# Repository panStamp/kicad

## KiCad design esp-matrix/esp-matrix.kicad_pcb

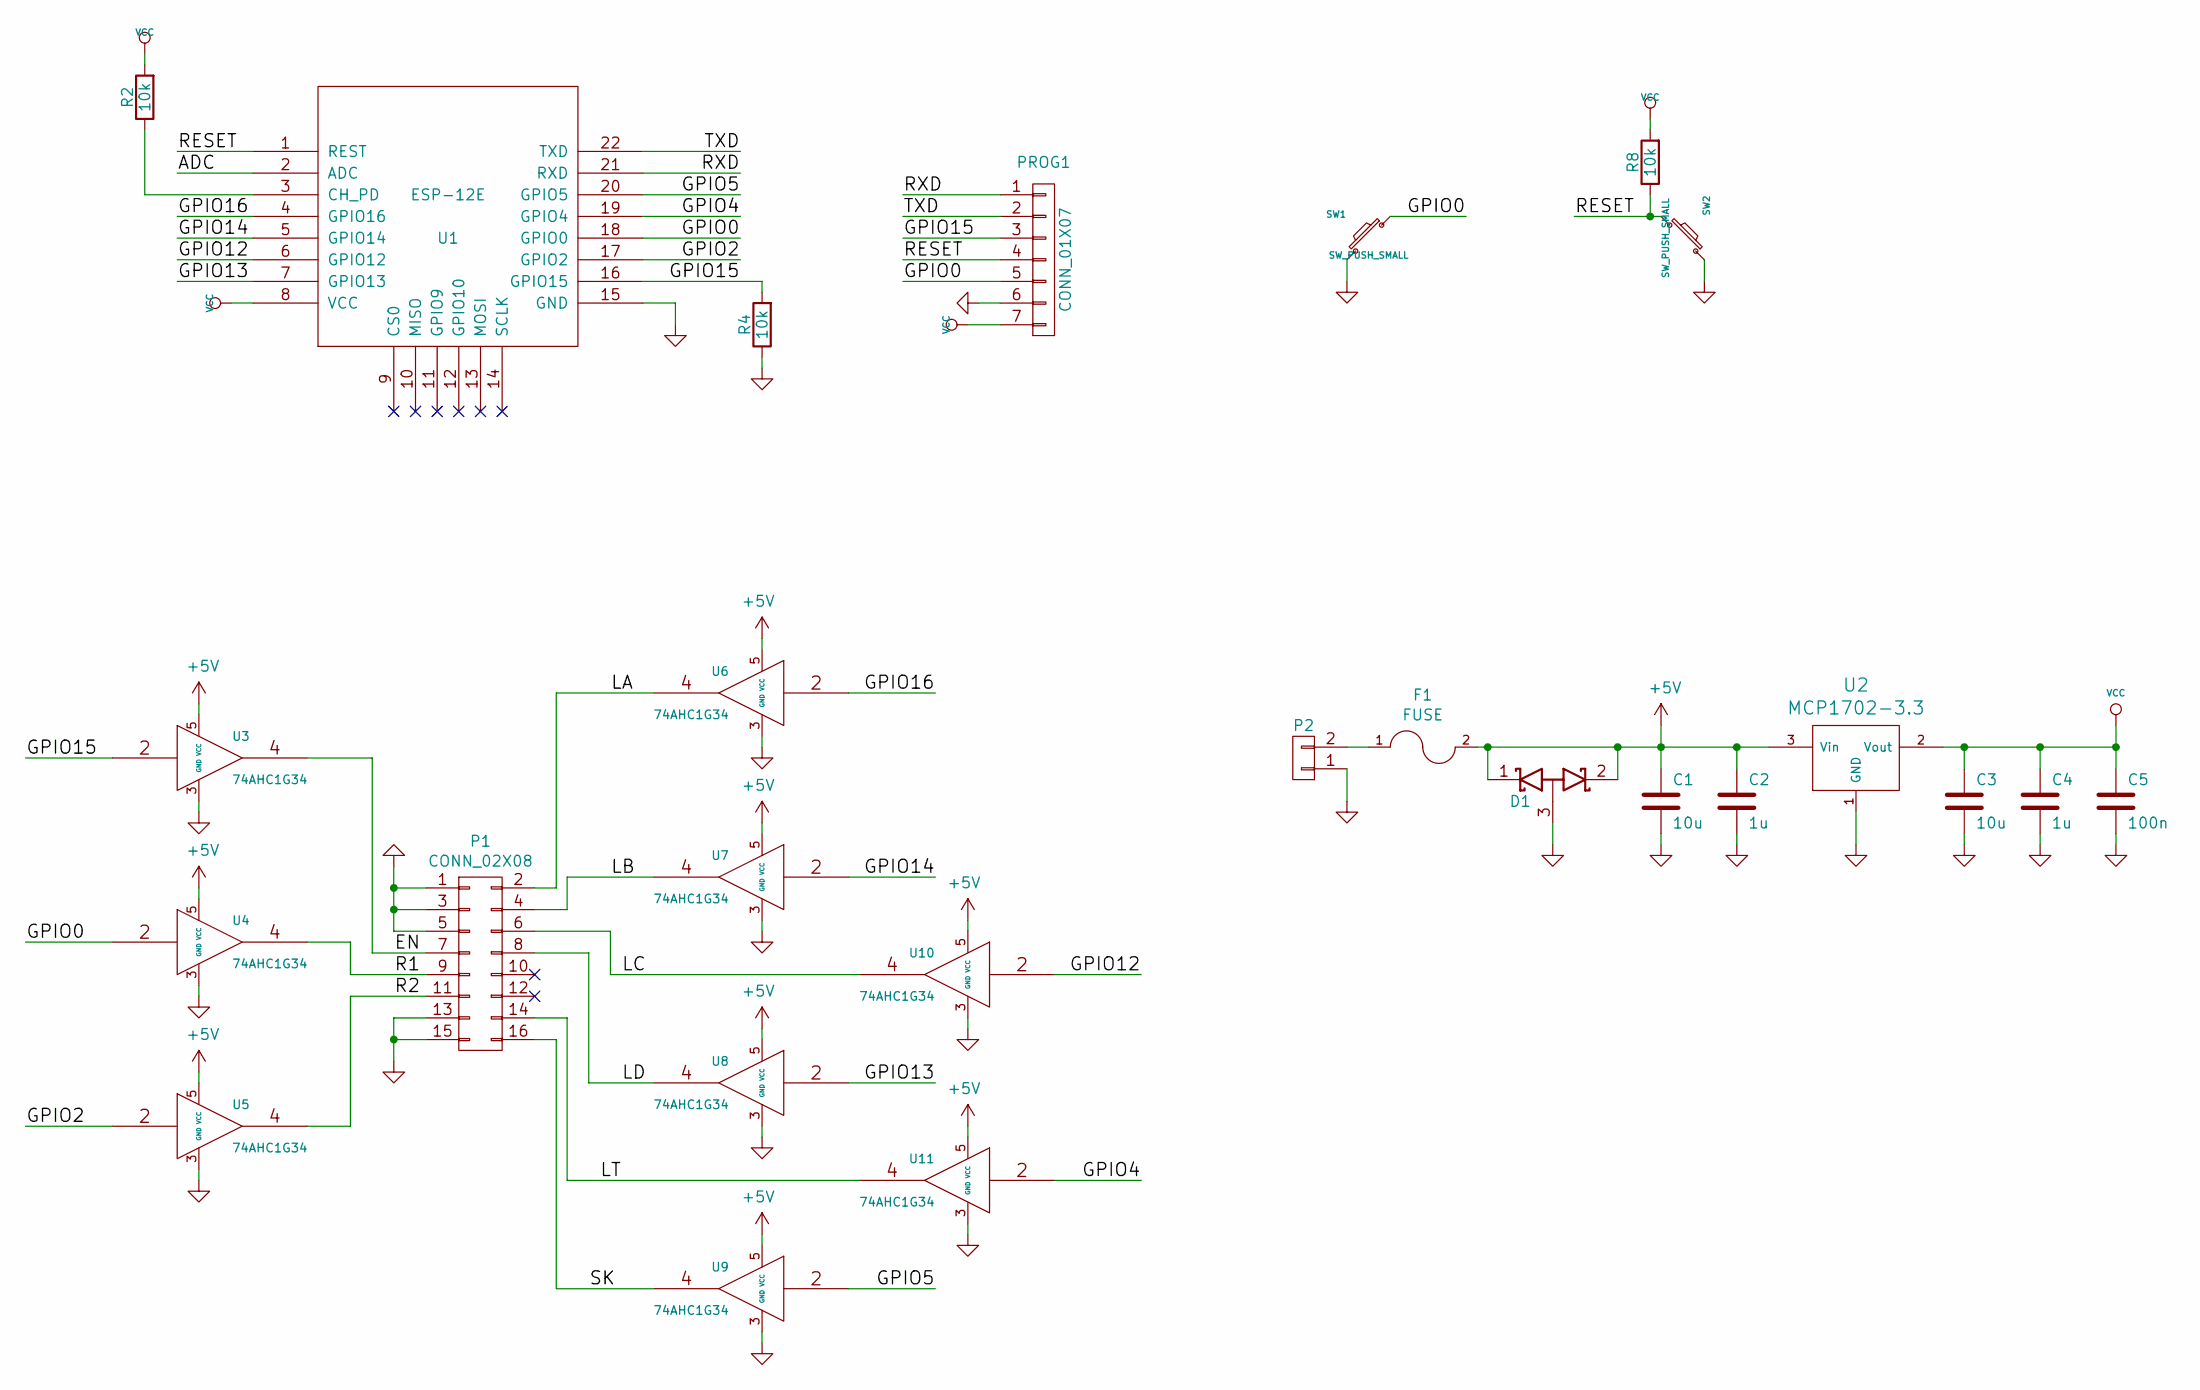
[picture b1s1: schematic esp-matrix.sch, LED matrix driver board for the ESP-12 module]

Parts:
C1, C3: 10u; SM0603S
C2, C4: 1u; SM0603S
C5: 100n; SM0603S
D1: D_Schottky_x2_ACom_KKA; SOT23
F1: FUSE; SM0805
P1: CONN_02X08; Pin_Header_Straight_2x08
P2: CONN_01X02; terminal_block_5mm_2P
PROG1: CONN_01X07; pinhead-1-1X07
R2, R4, R8: 10k; SM0603S
SW1, SW2: SW_PUSH_SMALL; switch-tact-noah
U1: ESP-12E
U2: MCP1702-3.3; SOT23
U3, U4, U5, U6, U7, U8, U9, U10, U11: 74AHC1G34; SOT23-5

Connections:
+5V: C1.1, C2.1, D1.1 (K), D1.2 (K), F1.2, U2.3 (Vin), U3.5 (VCC), U4.5 (VCC), U5.5 (VCC), U6.5 (VCC), U7.5 (VCC), U8.5 (VCC), U9.5 (VCC), U10.5 (VCC), U11.5 (VCC)
/ADC: U1.2 (ADC)
/EN: P1.7, U3.4
/GPIO0: PROG1.5, SW1.1, U1.18 (GPIO0), U4.2
/GPIO2: U1.17 (GPIO2), U5.2
/GPIO4: U1.19 (GPIO4), U11.2
/GPIO5: U1.20 (GPIO5), U9.2
/GPIO12: U1.6 (GPIO12), U10.2
/GPIO13: U1.7 (GPIO13), U8.2
/GPIO14: U1.5 (GPIO14), U7.2
/GPIO15: PROG1.3, R4.2, U1.16 (GPIO15), U3.2
/GPIO16: U1.4 (GPIO16), U6.2
/LA: P1.2, U6.4
/LB: P1.4, U7.4
/LC: P1.6, U10.4
/LD: P1.8, U8.4
/LT: P1.14, U11.4
/R1: P1.9, U4.4
/R2: P1.11, U5.4
/RESET: PROG1.4, R8.1, SW2.2, U1.1 (REST)
/RXD: PROG1.1, U1.21 (RXD)
/SK: P1.16, U9.4
/TXD: PROG1.2, U1.22 (TXD)
GND: C1.2, C2.2, C3.2, C4.2, C5.2, D1.3 (A), P1.1, P1.3, P1.5, P1.13, P1.15, P2.1, PROG1.6, R4.1, SW1.2, SW2.1, U1.15 (GND), U2.1 (GND), U3.3 (GND), U4.3 (GND), U5.3 (GND), U6.3 (GND), U7.3 (GND), U8.3 (GND), U9.3 (GND), U10.3 (GND), U11.3 (GND)
unnamed: F1.1, P2.2
unnamed: R2.1, U1.3 (CH_PD)
VCC: C3.1, C4.1, C5.1, PROG1.7, R2.2, R8.2, U1.8 (VCC), U2.2 (Vout)

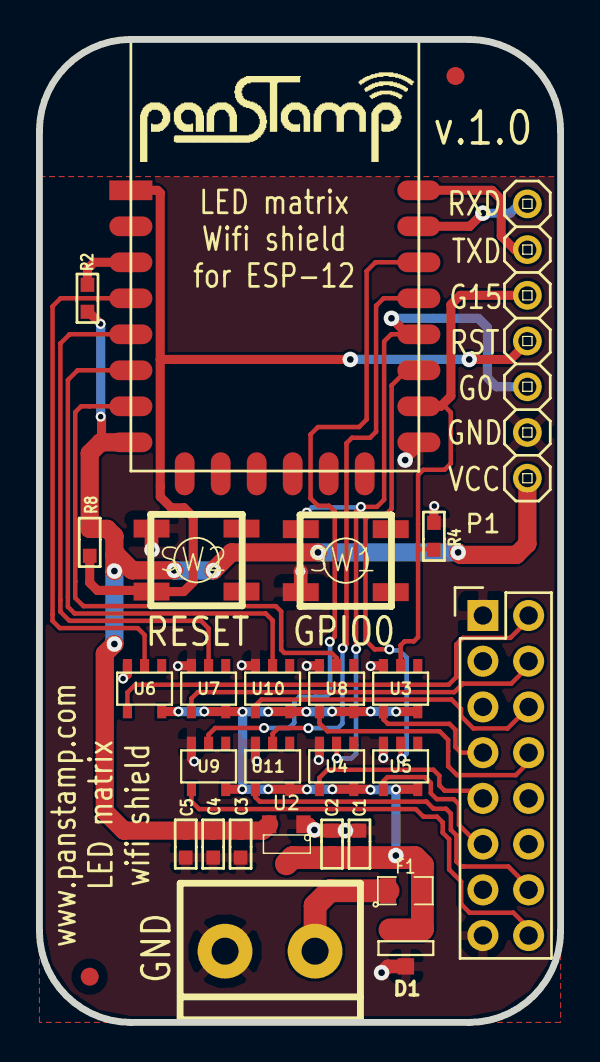
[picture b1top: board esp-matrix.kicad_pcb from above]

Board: 2 copper layers, 29.0 x 54.6 mm, 28 parts (0 on the bottom side), 26 nets.

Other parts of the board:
fiducial: VAL**; fiducial
fiducial#2: VAL**; fiducial

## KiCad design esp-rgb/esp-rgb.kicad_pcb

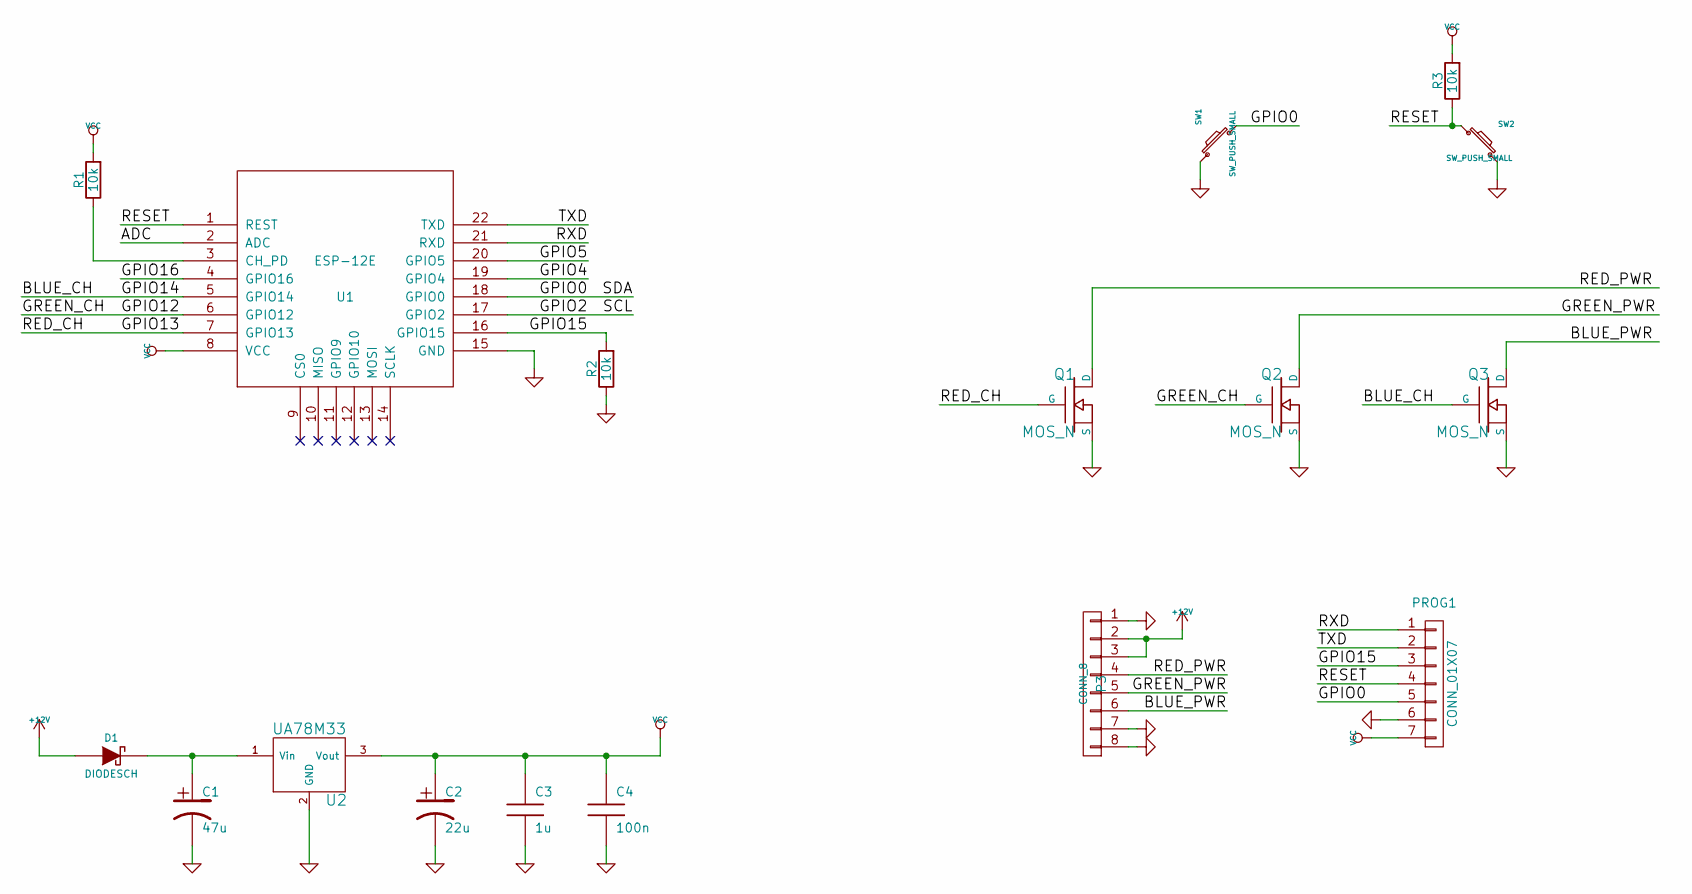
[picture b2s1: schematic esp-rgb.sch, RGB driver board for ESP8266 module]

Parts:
C1: 47u; SMDCPOL_6.3
C2: 22u; SMDCPOL_5
C3: 1u; SM0603S
C4: 100n; SM0603S
D1: DIODESCH; SMA
P3: CONN_8; Pin_Header_Straight_1x08
PROG1: CONN_01X07; Pin_Header_Straight_1x07
Q1, Q2, Q3: MOS_N; SOT23GDS
R1, R2, R3: 10k; SM0603S
SW1, SW2: SW_PUSH_SMALL; switch-tact-noah
U1: ESP-12E
U2: UA78M33; SOT223

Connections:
+12V: D1.1 (A), P3.2, P3.3
/ADC: U1.2 (ADC)
/BLUE_CH: Q3.G, U1.5 (GPIO14)
/BLUE_PWR: P3.6, Q3.D
/GPIO0: PROG1.5, SW1.2, U1.18 (GPIO0)
/GPIO2: U1.17 (GPIO2)
/GPIO4: U1.19 (GPIO4)
/GPIO5: U1.20 (GPIO5)
/GPIO12: Q2.G, U1.6 (GPIO12)
/GPIO13: Q1.G, U1.7 (GPIO13)
/GPIO15: PROG1.3, R2.2, U1.16 (GPIO15)
/GPIO16: U1.4 (GPIO16)
/GREEN_PWR: P3.5, Q2.D
/RED_PWR: P3.4, Q1.D
/RESET: PROG1.4, R3.1, SW2.1, U1.1 (REST)
/RXD: PROG1.1, U1.21 (RXD)
/TXD: PROG1.2, U1.22 (TXD)
GND: C1.2, C2.2, C3.2, C4.2, P3.1, P3.7, P3.8, PROG1.6, Q1.S, Q2.S, Q3.S, R2.1, SW1.1, SW2.2, U1.15 (GND), U2.2 (GND), U2.4
unnamed: C1.1, D1.2 (K), U2.1 (Vin)
unnamed: R1.1, U1.3 (CH_PD)
VCC: C2.1, C3.1, C4.1, PROG1.7, R1.2, R3.2, U1.8 (VCC), U2.3 (Vout)

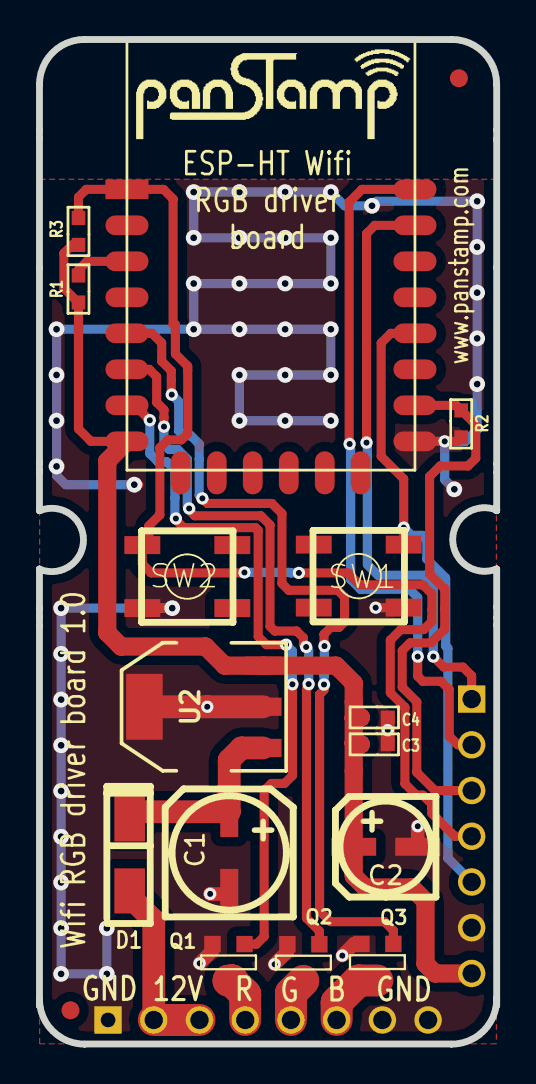
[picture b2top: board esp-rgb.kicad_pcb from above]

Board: 4 copper layers, 25.4 x 55.8 mm, 19 parts (0 on the bottom side), 16 nets.

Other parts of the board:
fiducial: VAL**; fiducial
fiducial#2: VAL**; fiducial

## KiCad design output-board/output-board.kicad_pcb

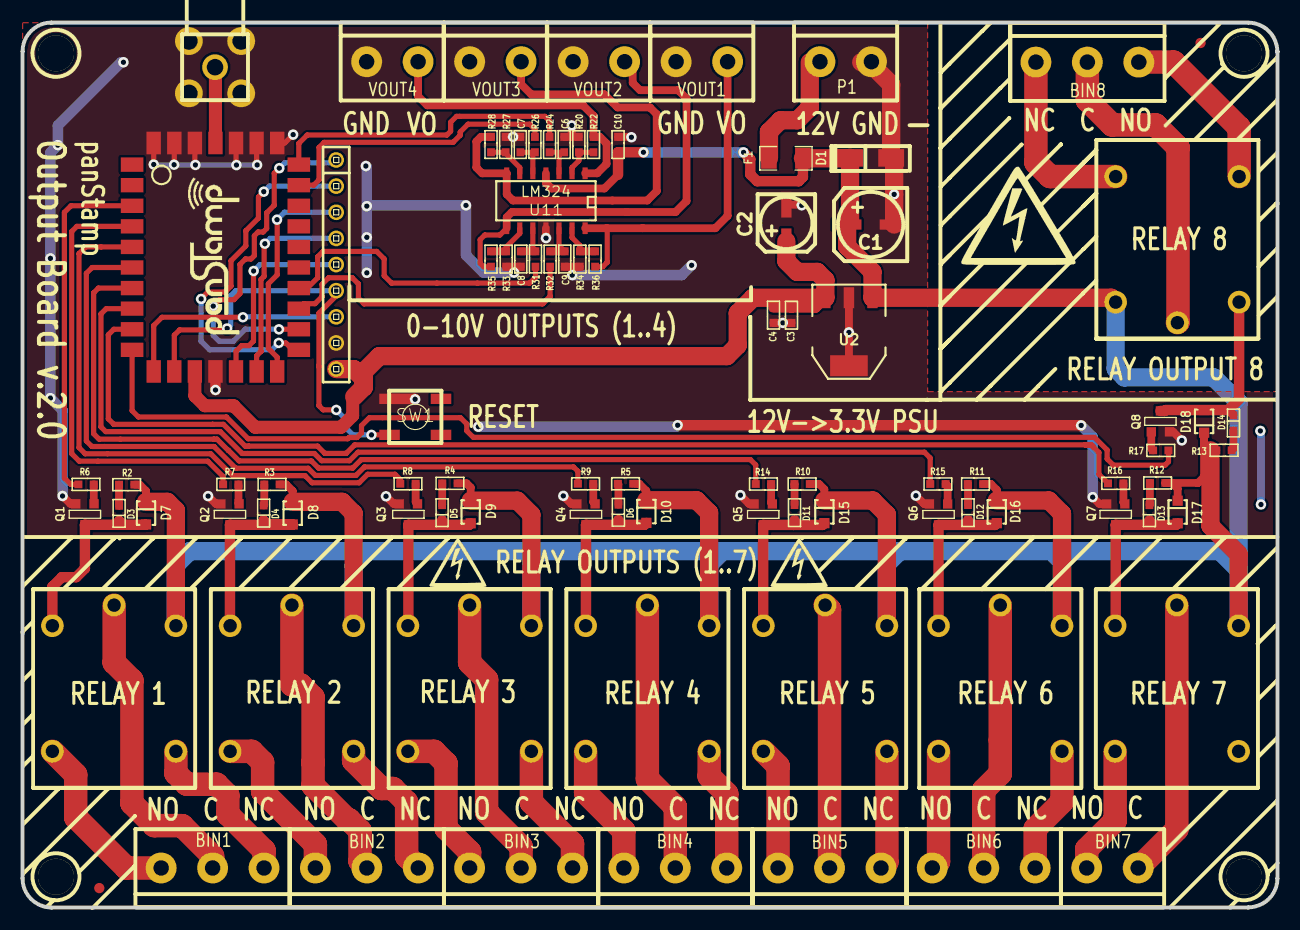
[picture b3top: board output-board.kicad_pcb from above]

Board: 2 copper layers, 121.9 x 86.0 mm, 96 parts (0 on the bottom side), 83 nets.

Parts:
1PIN, 1PIN#2, 1PIN#3, 1PIN#4: P***; 1pin
BIN1, BIN2, BIN3, BIN4, BIN5, BIN6, BIN8: CONN_3; terminal_block_5mm_3P
BIN7: CONN_2; terminal_block_5mm_2P
C1: 47u; SMDCPOL_6.3
C2: 22u; SMDCPOL_5
C3: 1u; SM0603S
C4, C10: 100n; SM0603S
C6, C7, C8, C9: 4.7u; SM0603S
D1: DIODESCH; SMA
D3, D4, D5, D6, D11, D12, D13, D14: LED; SM0603S_POL
D7, D8, D9, D10, D15, D16, D17, D18: DIODE; SOD323
F1: FUSE; SM1206
P1: CONN_2; terminal_block_5mm_2P
P2: CONN_01X09; pinhead-1X09
PS1: PANSTAMP_NRG2; PANSTAMP_2
Q1, Q2, Q3, Q4, Q5, Q6, Q7, Q8: NPN; SOT23EBC
R2, R3, R4, R5, R10, R11, R12, R13: 1k5; SM0603S
R6, R7, R8, R9, R14, R15, R16, R17: 2k2; SM0603S
R20, R27, R33, R34: 10k; SM0603S
R22, R28, R35, R36: 21k; SM0603S
R24, R26, R31, R32: 10K; SM0603S
SW1: SW_PUSH_SMALL; switch-tact-noah
U1: ANTENNA; SMA_RightAngle_Tyco
U2: UA78M33; SOT223
U3, U4, U5, U6, U7, U8, U9, U10: SONGLE_RELAY_10A
U11: LM324; SO14E
VOUT1, VOUT2, VOUT3, VOUT4: CONN_2; terminal_block_5mm_2P
fiducial: VAL**; fiducial
fiducial#2: VAL**; fiducial

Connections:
+3.3V: C2.1, C3.1, C4.1, P2.9, PS1.13, U2.3
+12V: C1.1, C10.1, D1.2, D7.2, D8.2, D9.2, D10.2, D15.2, D16.2, D17.2, D18.2, F1.2, R2.2, R3.1, R4.1, R5.1, R10.1, R11.1, R12.1, R13.1, U2.1, U3.1, U4.1, U5.1, U6.1, U7.1, U8.1, U9.1, U10.1, U11.4
/D7: P2.5, PS1.15
/RESET: P2.6, PS1.12, SW1.2
/RXD: P2.3, PS1.17
/SCL: P2.2, PS1.18
/SDA: P2.1, PS1.19
/TEST: P2.7, PS1.11
/TXD: P2.4, PS1.16
BINOUT0: PS1.3, R6.1
BINOUT1: PS1.4, R7.1
BINOUT2: PS1.5, R8.1
BINOUT3: PS1.6, R9.1
BINOUT4: PS1.7, R14.1
BINOUT5: PS1.8, R15.1
BINOUT6: PS1.9, R16.1
BINOUT7: PS1.10, R17.1
GND: C1.2, C2.2, C3.2, C4.2, C6.2, C7.2, C8.2, C9.2, C10.2, D1.1, P1.1, P2.8, PS1.14, PS1.28, PS1.29, PS1.30, PS1.32, PS1.33, PS1.34, Q1.1, Q2.1, Q3.1, Q4.1, Q5.1, Q6.1, Q7.1, Q8.1, R20.1, R27.1, R33.1, R34.1, SW1.1, U1.2, U2.2, U2.4, U11.11, VOUT1.2, VOUT2.2, VOUT3.2, VOUT4.2
unnamed: BIN1.1, U3.4
unnamed: BIN1.2, U3.2
unnamed: BIN1.3, U3.5
unnamed: BIN2.1, U4.4
unnamed: BIN2.2, U4.2
unnamed: BIN2.3, U4.5
unnamed: BIN3.1, U5.4
unnamed: BIN3.2, U5.2
unnamed: BIN3.3, U5.5
unnamed: BIN4.1, U6.4
unnamed: BIN4.2, U6.2
unnamed: BIN4.3, U6.5
unnamed: BIN5.1, U7.4
unnamed: BIN5.2, U7.2
unnamed: BIN5.3, U7.5
unnamed: BIN6.1, U8.4
unnamed: BIN6.2, U8.2
unnamed: BIN6.3, U8.5
unnamed: BIN7.1, U9.4
unnamed: BIN7.2, U9.2
unnamed: BIN8.1, U10.4
unnamed: BIN8.2, U10.2
unnamed: BIN8.3, U10.5
unnamed: C6.1, R24.1, U11.3
unnamed: C7.1, R26.1, U11.5
unnamed: C8.1, R31.1, U11.10
unnamed: C9.1, R32.1, U11.12
unnamed: D3.1, R2.1
unnamed: D3.2, D7.1, Q1.3, U3.3
unnamed: D4.1, R3.2
unnamed: D4.2, D8.1, Q2.3, U4.3
unnamed: D5.1, R4.2
unnamed: D5.2, D9.1, Q3.3, U5.3
unnamed: D6.1, R5.2
unnamed: D6.2, D10.1, Q4.3, U6.3
unnamed: D11.1, R10.2
unnamed: D11.2, D15.1, Q5.3, U7.3
unnamed: D12.1, R11.2
unnamed: D12.2, D16.1, Q6.3, U8.3
unnamed: D13.1, R12.2
unnamed: D13.2, D17.1, Q7.3, U9.3
unnamed: D14.1, R13.2
unnamed: D14.2, D18.1, Q8.3, U10.3
unnamed: F1.1, P1.2
unnamed: PS1.31, U1.1
unnamed: Q1.2, R6.2
unnamed: Q2.2, R7.2
unnamed: Q3.2, R8.2
unnamed: Q4.2, R9.2
unnamed: Q5.2, R14.2
unnamed: Q6.2, R15.2
unnamed: Q7.2, R16.2
unnamed: Q8.2, R17.2
unnamed: R20.2, R22.1, U11.2
unnamed: R22.2, U11.1, VOUT4.1
unnamed: R27.2, R28.1, U11.6
unnamed: R28.2, U11.7, VOUT3.1
unnamed: R33.2, R35.1, U11.9
unnamed: R34.2, R36.1, U11.13
unnamed: R35.2, U11.8, VOUT2.1
unnamed: R36.2, U11.14, VOUT1.1
PWMOUT0: PS1.27, R24.2
PWMOUT1: PS1.26, R26.2
PWMOUT2: PS1.21, R31.2
PWMOUT3: PS1.20, R32.2

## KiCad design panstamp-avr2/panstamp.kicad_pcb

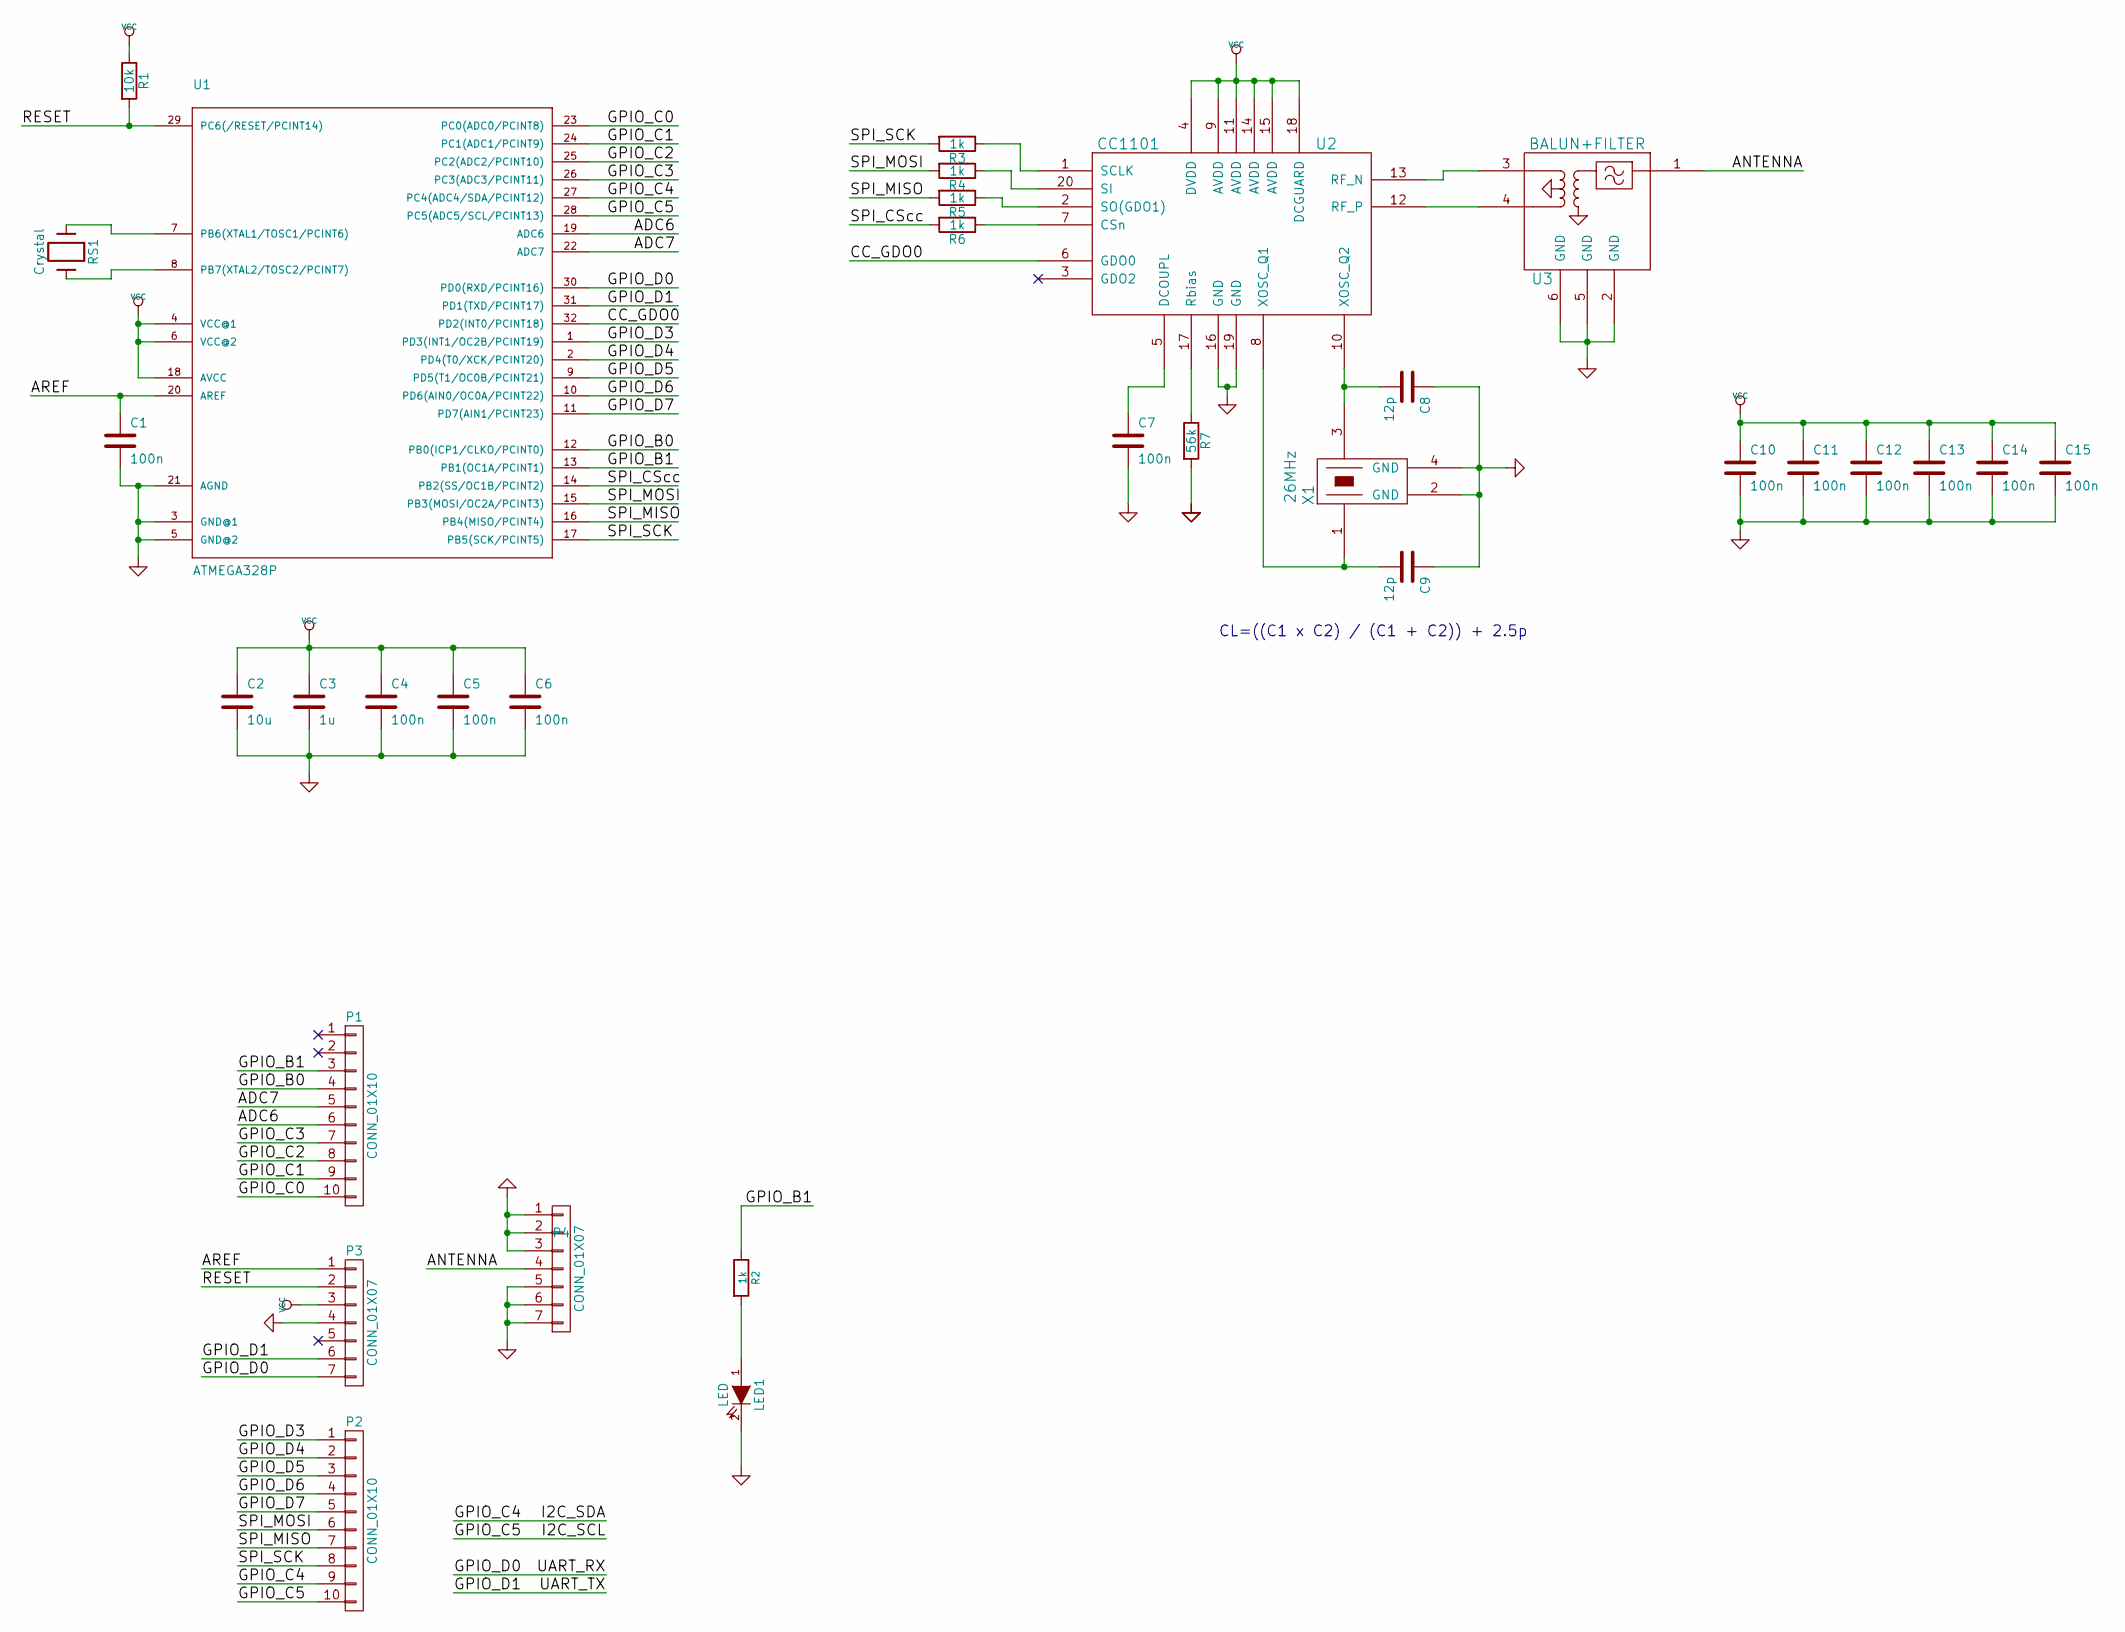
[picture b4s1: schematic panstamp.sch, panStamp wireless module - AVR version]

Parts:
C1, C4, C5, C6, C7, C10, C11, C12, C13, C14, C15: 100n; SM0603S
C2: 10u; SM0603S
C3: 1u; SM0603S
C8, C9: 12p; SM0603S
LED1: LED; SM0603S_POL
P1, P2: CONN_01X10; CASTELLATED_2MM_10
P3, P4: CONN_01X07; CASTELLATED_2MM_7
R1: 10k; SM0603S
R2, R3, R4, R5, R6: 1k; SM0603S
R7: 56k; SM0603S
RS1: Crystal
U1: ATMEGA328P; avr-MLF32
U2: CC1101; QLP20
U3: BALUN+FILTER; JTI_Balun
X1: 26MHz; FCX-162

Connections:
/ADC6: P1.6, U1.19 (ADC6)
/ADC7: P1.5, U1.22 (ADC7)
/ANTENNA: P4.4, U3.1
/AREF: C1.1, P3.1, U1.20 (AREF)
/CC_GDO0: U1.32 (PD2(INT0/PCINT18)), U2.6 (GDO0)
/GPIO_B0: P1.4, U1.12 (PB0(ICP1/CLKO/PCINT0))
/GPIO_B1: P1.3, R2.1, U1.13 (PB1(OC1A/PCINT1))
/GPIO_C0: P1.10, U1.23 (PC0(ADC0/PCINT8))
/GPIO_C1: P1.9, U1.24 (PC1(ADC1/PCINT9))
/GPIO_C2: P1.8, U1.25 (PC2(ADC2/PCINT10))
/GPIO_C3: P1.7, U1.26 (PC3(ADC3/PCINT11))
/GPIO_C4: P2.9, U1.27 (PC4(ADC4/SDA/PCINT12))
/GPIO_C5: P2.10, U1.28 (PC5(ADC5/SCL/PCINT13))
/GPIO_D0: P3.7, U1.30 (PD0(RXD/PCINT16))
/GPIO_D1: P3.6, U1.31 (PD1(TXD/PCINT17))
/GPIO_D3: P2.1, U1.1 (PD3(INT1/OC2B/PCINT19))
/GPIO_D4: P2.2, U1.2 (PD4(T0/XCK/PCINT20))
/GPIO_D5: P2.3, U1.9 (PD5(T1/OC0B/PCINT21))
/GPIO_D6: P2.4, U1.10 (PD6(AIN0/OC0A/PCINT22))
/GPIO_D7: P2.5, U1.11 (PD7(AIN1/PCINT23))
/RESET: P3.2, R1.2, U1.29 (PC6(/RESET/PCINT14))
/SPI_CScc: R6.2, U1.14 (PB2(SS/OC1B/PCINT2))
/SPI_MISO: P2.7, R5.2, U1.16 (PB4(MISO/PCINT4))
/SPI_MOSI: P2.6, R4.2, U1.15 (PB3(MOSI/OC2A/PCINT3))
/SPI_SCK: P2.8, R3.2, U1.17 (PB5(SCK/PCINT5))
GND: C1.2, C2.2, C3.2, C4.2, C5.2, C6.2, C7.2, C8.1, C9.1, C10.2, C11.2, C12.2, C13.2, C14.2, C15.2, LED1.2 (K), P3.4, P4.1, P4.2, P4.3, P4.5, P4.6, P4.7, R7.2, U1.3 (GND@1), U1.5 (GND@2), U1.21 (AGND), U2.16 (GND), U2.19 (GND), U3.2 (GND), U3.5 (GND), U3.6 (GND), X1.2 (GND), X1.4 (GND)
unnamed: C7.1, U2.5 (DCOUPL)
unnamed: C8.2, U2.10 (XOSC_Q2), X1.3
unnamed: C9.2, U2.8 (XOSC_Q1), X1.1
unnamed: LED1.1 (A), R2.2
unnamed: R3.1, U2.1 (SCLK)
unnamed: R4.1, U2.20 (SI)
unnamed: R5.1, U2.2 (SO(GDO1))
unnamed: R6.1, U2.7 (CSn)
unnamed: R7.1, U2.17 (Rbias)
unnamed: RS1.1, U1.7 (PB6(XTAL1/TOSC1/PCINT6))
unnamed: RS1.2, U1.8 (PB7(XTAL2/TOSC2/PCINT7))
unnamed: U2.12 (RF_P), U3.4
unnamed: U2.13 (RF_N), U3.3
VCC: C2.1, C3.1, C4.1, C5.1, C6.1, C10.1, C11.1, C12.1, C13.1, C14.1, C15.1, P3.3, R1.1, U1.4 (VCC@1), U1.6 (VCC@2), U1.18 (AVCC), U2.4 (DVDD), U2.9 (AVDD), U2.11 (AVDD), U2.14 (AVDD), U2.15 (AVDD), U2.18 (DCGUARD)

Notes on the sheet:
CL=((C1 x C2) / (C1 + C2)) + 2.5p

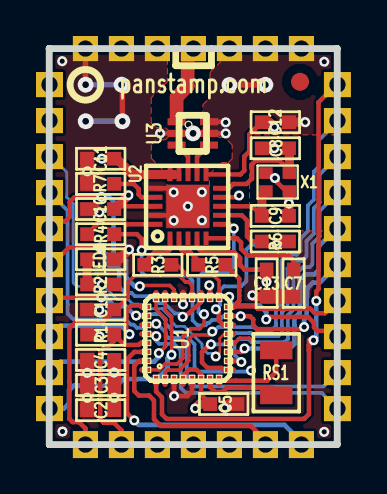
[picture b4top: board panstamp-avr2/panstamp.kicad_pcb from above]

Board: 4 copper layers, 16.0 x 22.0 mm, 30 parts (0 on the bottom side), 40 nets.

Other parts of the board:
fiducial: VAL**; fiducial

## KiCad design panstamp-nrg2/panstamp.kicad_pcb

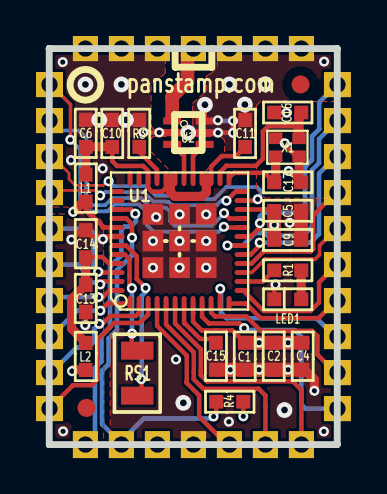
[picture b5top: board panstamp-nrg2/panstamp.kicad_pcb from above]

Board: 4 copper layers, 16.0 x 22.0 mm, 29 parts (0 on the bottom side), 40 nets.

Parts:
C1, C14: 10u; SM0603S
C2: 1u; SM0603S
C4, C5, C6, C11, C13: 100n; SM0603S
C9: 10n; SM0603S
C10: 2p; SM0603S
C15: 470nF; SM0603S
C16, C17: 12p; SM0603S
L1, L2: 600R/200mA; SM0603S
LED1: LED; SM0603S_POL
P1, P2: CONN_01X10; CASTELLATED_2MM_10
P3, P4: CONN_01X07; CASTELLATED_2MM_7
R1: 1k; SM0603S
R3: 56k(1%); SM0603S
R4: 47k; SM0603S
RS1: 32.768KHz; EPSON_F-135
U1: CC430F5137; VQFN48
U2: BALUN+FILTER; JTI_Balun
X1: 26MHz; FCX-162
fiducial: VAL**; fiducial
fiducial#2: VAL**; fiducial

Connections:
/#RST/SBWTDIO: P3.2, R4.2, U1.40
/ANTENNA: P4.4, U2.1
/I2C_SCL: P2.10, U1.9
/I2C_SDA: P2.9, U1.10
/P1.0: P2.6, U1.13
/P1.1: P2.7, U1.12
/P1.2: P2.8, U1.11
/P1.5: P3.7, U1.6
/P1.6: P3.6, U1.5
/P1.7: P3.5, U1.4
/P2.0/A0: P1.10, U1.3
/P2.1/A1: P1.9, U1.2
/P2.2/A2: P1.8, U1.1
/P2.3/A3: P1.7, U1.48
/P2.4/A4: P1.6, U1.47
/P2.5/A5: P1.5, U1.46
/P2.6: P1.4, U1.24
/P2.7: P1.3, U1.23
/P3.0: P1.2, U1.21
/P3.1: P1.1, U1.20
/P3.2: P2.1, U1.19
/P3.3: P2.2, U1.18
/P3.4: P2.3, U1.17
/P3.5: P2.4, U1.16
/P3.6: P2.5, U1.15
/P3.7: R1.1, U1.14
/RF_N: U1.30, U2.3
/RF_P: U1.29, U2.4
/TEST/SBWTCK: P3.1, U1.39
GND: C1.2, C2.2, C4.2, C5.2, C6.2, C9.2, C10.2, C11.2, C13.1, C14.1, C15.1, C16.2, C17.2, LED1.2, P3.4, P4.1, P4.2, P4.3, P4.5, P4.6, P4.7, R3.2, U1.42, U1.VSS, U2.2, U2.5, U2.6, X1.2, X1.4
unnamed: C6.1, C10.1, C11.1, L1.2, U1.27, U1.28, U1.31, U1.32, U1.34
unnamed: C13.2, C14.2, L2.2, U1.45
unnamed: C15.2, U1.7
unnamed: C16.1, U1.26, X1.1
unnamed: C17.1, U1.25, X1.3
unnamed: LED1.1, R1.2
unnamed: R3.1, U1.33
unnamed: RS1.1, U1.44
unnamed: RS1.2, U1.43
VCC: C1.1, C2.1, C4.1, C5.1, C9.1, L1.1, L2.1, P3.3, R4.1, U1.8, U1.22, U1.41

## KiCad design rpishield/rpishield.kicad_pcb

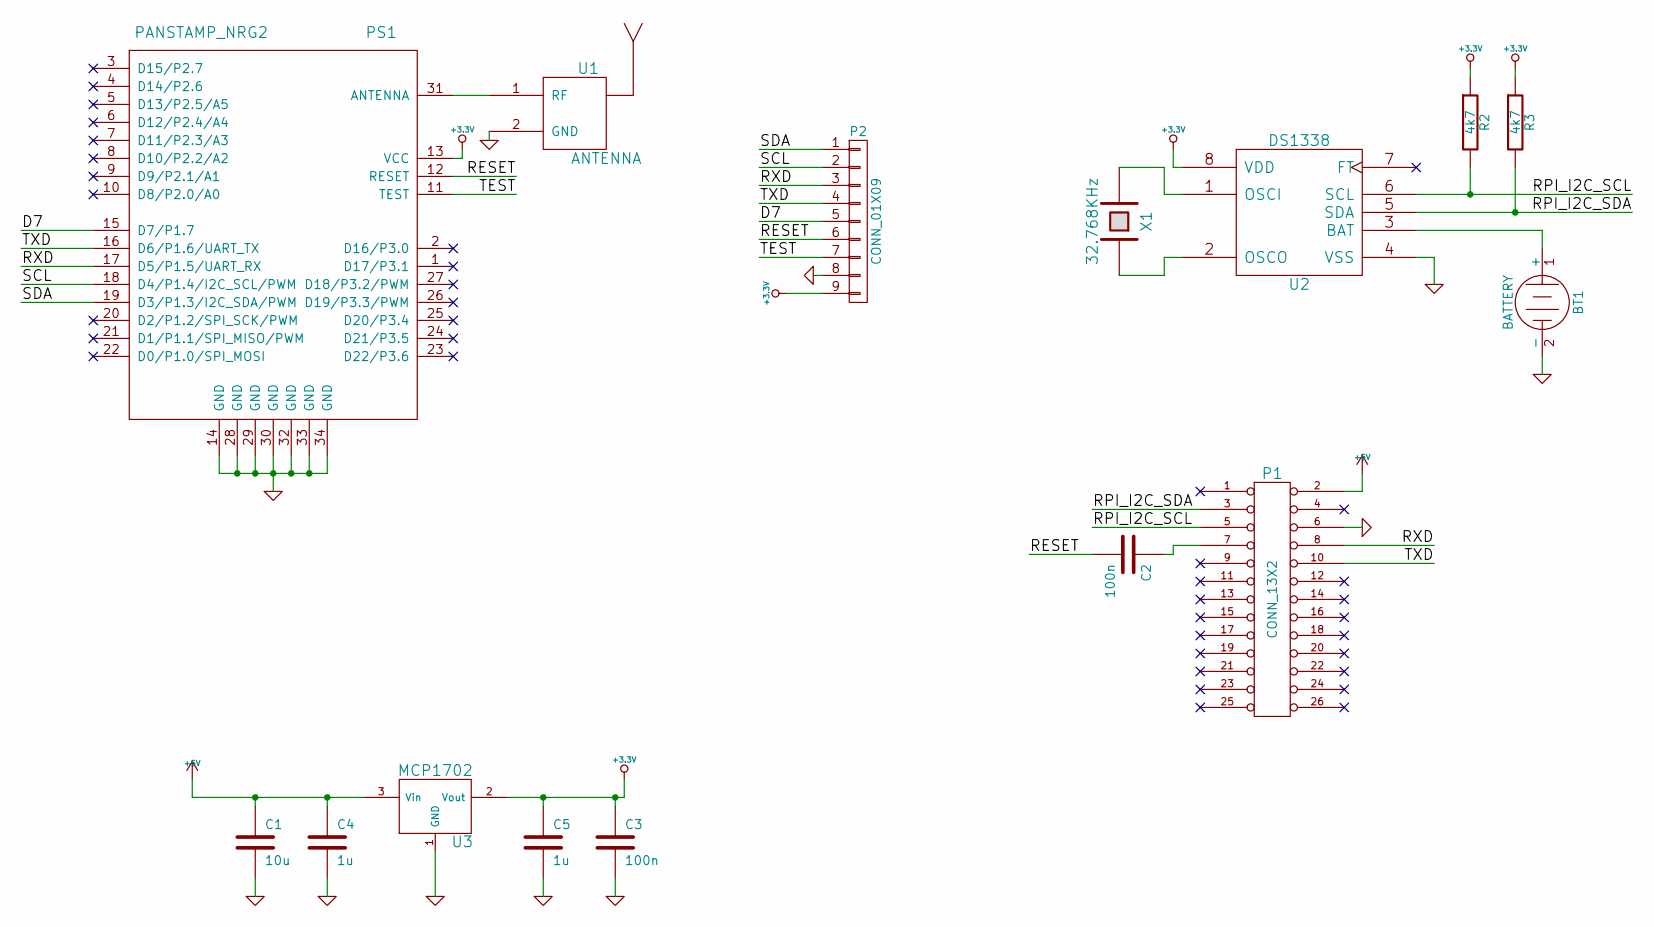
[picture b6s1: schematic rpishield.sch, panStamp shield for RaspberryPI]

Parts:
BT1: BATTERY; linx_bat-hld-001
C1: 10u; SM0603S
C2, C3: 100n; SM0603S
C4, C5: 1u; SM0603S
P1: CONN_13X2; pin_array_13x2
P2: CONN_01X09; Pin_Header_Straight_1x09
PS1: PANSTAMP_NRG2; PANSTAMP_2
R2, R3: 4k7; SM0603S
U1: ANTENNA; SMA_RightAngle_Tyco
U2: DS1338; SO8E
U3: MCP1702; SOT23
X1: 32.768KHz; EPSON_F-135

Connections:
+3.3V: C3.1, C5.1, P2.9, PS1.13 (VCC), R2.1, R3.1, U2.8 (VDD), U3.2 (Vout)
+5V: C1.1, C4.1, P1.2, U3.3 (Vin)
/D7: P2.5, PS1.15 (D7/P1.7)
/RESET: C2.2, P2.6, PS1.12 (RESET)
/RPI_I2C_SCL: P1.5, R2.2, U2.6 (SCL)
/RPI_I2C_SDA: P1.3, R3.2, U2.5 (SDA)
/RXD: P1.8, P2.3, PS1.17 (D5/P1.5/UART_RX)
/SCL: P2.2, PS1.18 (D4/P1.4/I2C_SCL/PWM)
/SDA: P2.1, PS1.19 (D3/P1.3/I2C_SDA/PWM)
/TEST: P2.7, PS1.11 (TEST)
/TXD: P1.10, P2.4, PS1.16 (D6/P1.6/UART_TX)
GND: BT1.2 (-), C1.2, C3.2, C4.2, C5.2, P1.6, P2.8, PS1.14 (GND), PS1.28 (GND), PS1.29 (GND), PS1.30 (GND), PS1.32 (GND), PS1.33 (GND), PS1.34 (GND), U1.2 (GND), U2.4 (VSS), U3.1 (GND)
unnamed: BT1.1 (+), U2.3 (BAT)
unnamed: C2.1, P1.7
unnamed: PS1.31 (ANTENNA), U1.1 (RF)
unnamed: U2.1 (OSCI), X1.2
unnamed: U2.2 (OSCO), X1.1

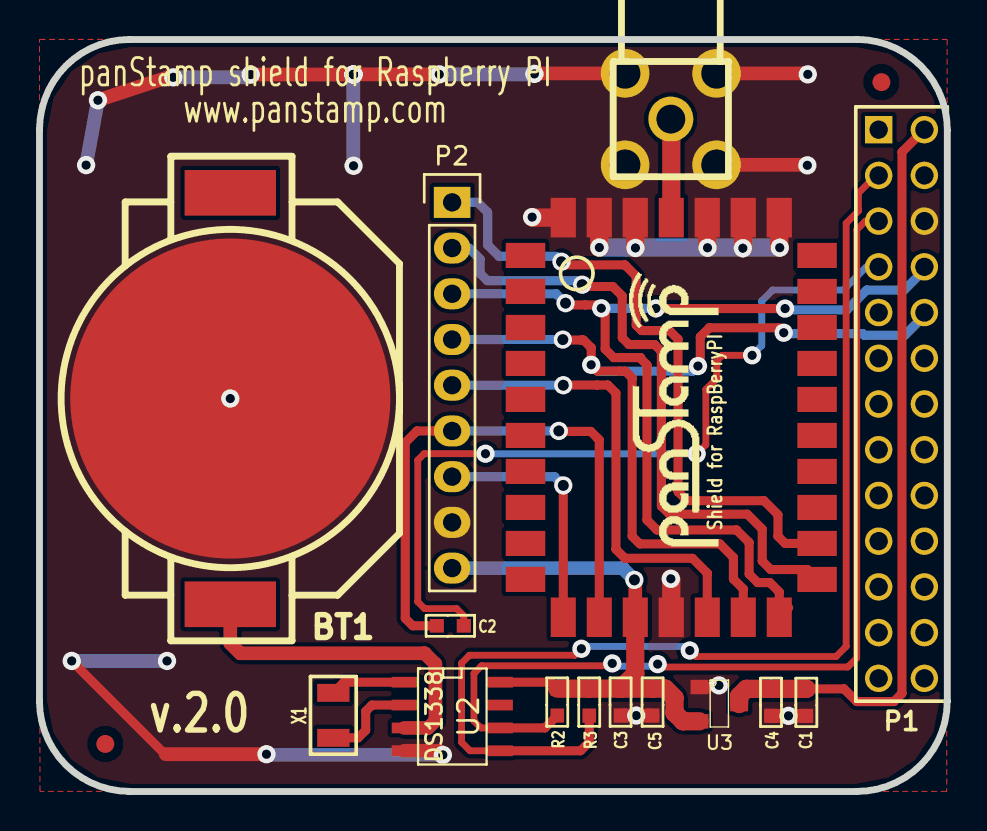
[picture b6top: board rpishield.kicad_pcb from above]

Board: 2 copper layers, 50.4 x 41.8 mm, 18 parts (0 on the bottom side), 17 nets.

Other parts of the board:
fiducial: VAL**; fiducial
fiducial#2: VAL**; fiducial
v.2.0: Shield for RaspBerryPI; PANSTAMPLOGO
